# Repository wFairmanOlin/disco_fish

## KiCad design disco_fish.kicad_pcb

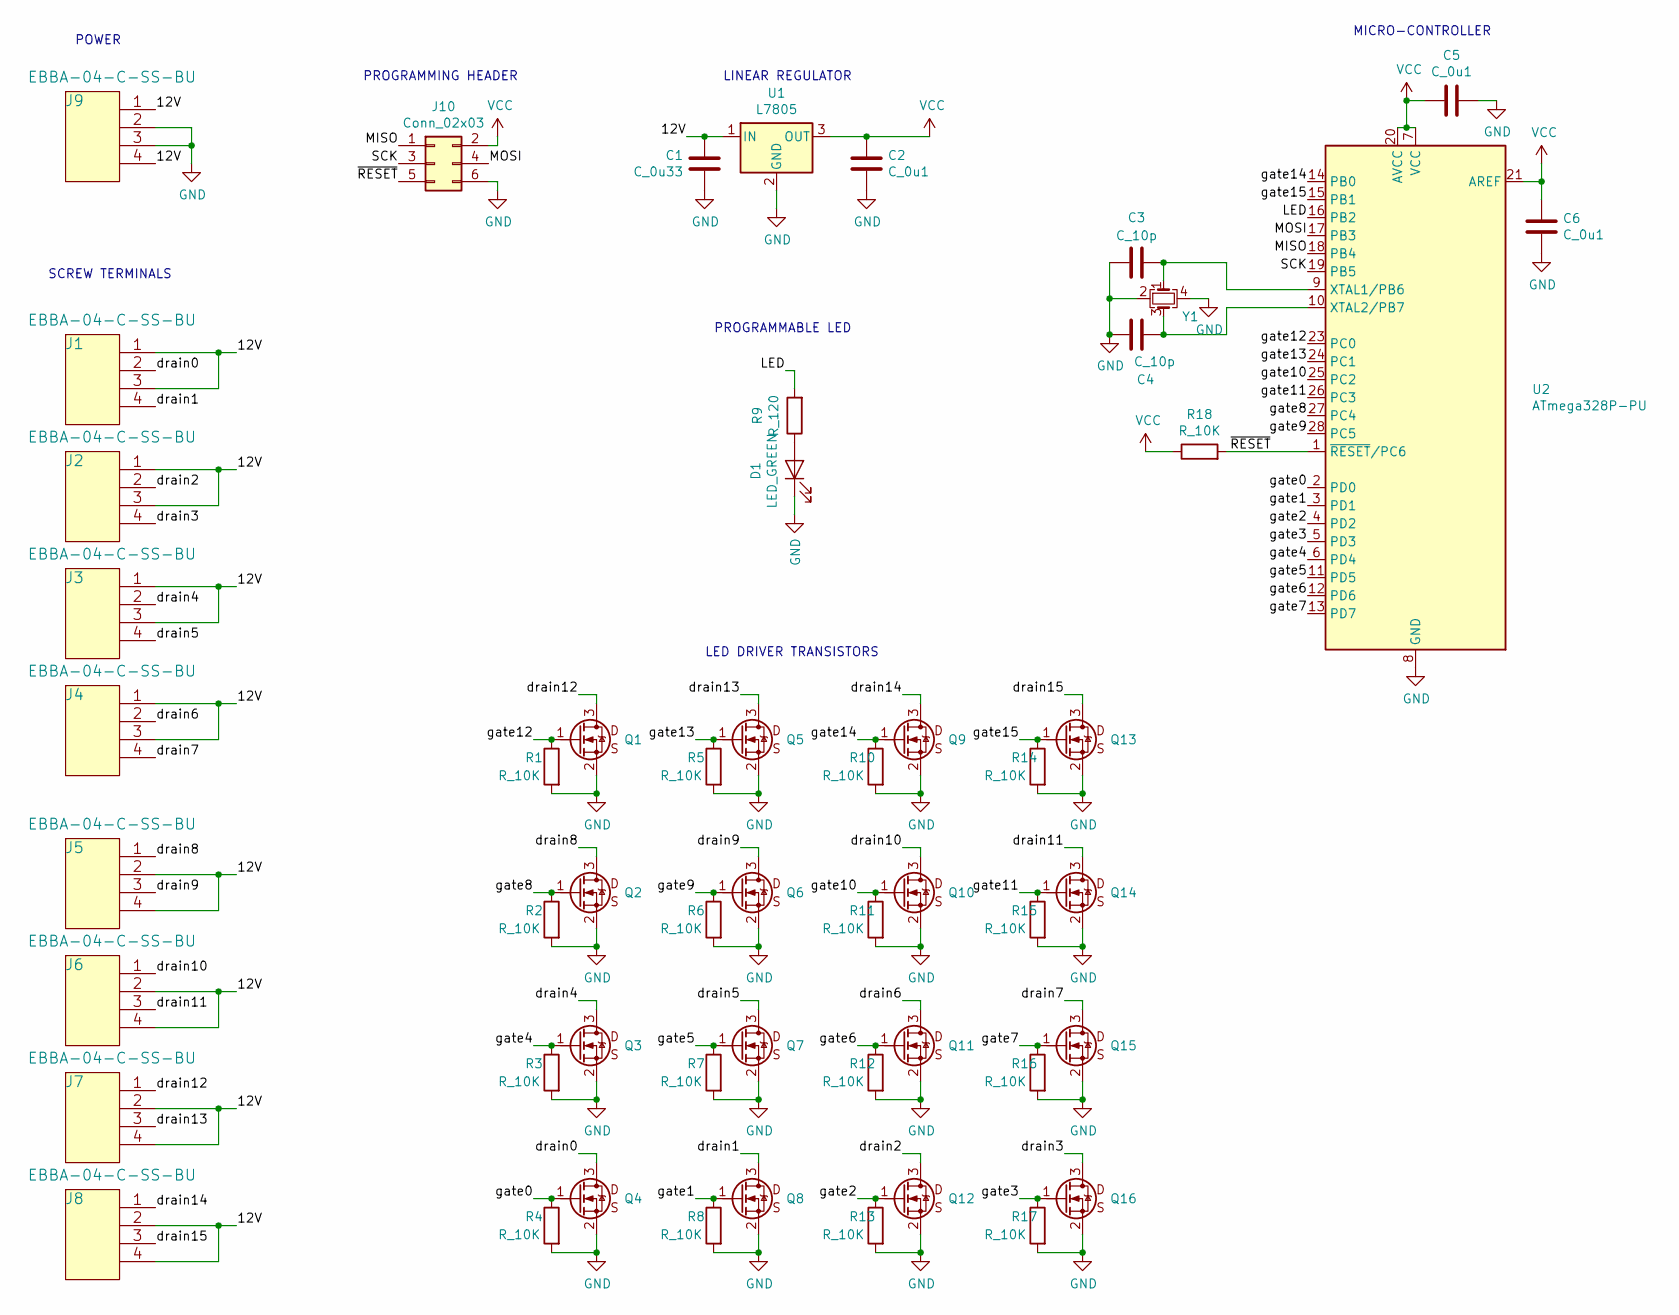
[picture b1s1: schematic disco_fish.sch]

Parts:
C1: C_0u33; C_0805; MPN CL21B334KBFNNNE
C2, C5, C6: C_0u1; C_0805
C3, C4: C_10p; C_0805; MPN 885012007010
D1: LED_GREEN; LED_0603_HandSoldering
J1, J2, J3, J4, J5, J6, J7, J8, J9: EBBA-04-C-SS-BU; MPN EBBA-04-C-SS-BU
J10: Conn_02x03; TSW-103-07-F-D; MPN TSW-103-07-F-D
Q1, Q2, Q3, Q4, Q5, Q6, Q7, Q8, Q9, Q10, Q11, Q12, Q13, Q14, Q15, Q16: NVS4409NT1G; SOT-323_SC-70; MPN NVS4409NT1G
R1, R2, R3, R4, R5, R6, R7, R8, R10, R11, R12, R13, R14, R15, R16, R17, R18: R_10K; R_0805; MPN RC0805FR-0710KL
R9: R_120; R_0805
U1: L7805; TO-252-2; MPN L7805CDT-TR
U2: ATmega328P-PU; DIP-28_W7.62mm; MPN ATMEGA328-PU
Y1: ECS-160-8-37-CWY-TR; 7M-16.000MAAJ-T; MPN ECS-160-8-37-CWY-TR

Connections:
/12V: C1.2, J1.1, J1.3, J2.1, J2.3, J3.1, J3.3, J4.1, J4.3, J5.2, J5.4, J6.2, J6.4, J7.2, J7.4, J8.2, J8.4, J9.1, J9.4, U1.1 (IN)
/LED: R9.2, U2.16 (PB2)
/MISO: J10.1, U2.18 (PB4)
/MOSI: J10.4, U2.17 (PB3)
/SCK: J10.3, U2.19 (PB5)
/drain0: J1.2, Q4.3
/drain1: J1.4, Q8.3
/drain2: J2.2, Q12.3
/drain3: J2.4, Q16.3
/drain4: J3.2, Q3.3
/drain5: J3.4, Q7.3
/drain6: J4.2, Q11.3
/drain7: J4.4, Q15.3
/drain8: J5.1, Q2.3
/drain9: J5.3, Q6.3
/drain10: J6.1, Q10.3
/drain11: J6.3, Q14.3
/drain12: J7.1, Q1.3
/drain13: J7.3, Q5.3
/drain14: J8.1, Q9.3
/drain15: J8.3, Q13.3
/gate0: Q4.1, R4.1, U2.2 (PD0)
/gate1: Q8.1, R8.1, U2.3 (PD1)
/gate2: Q12.1, R13.1, U2.4 (PD2)
/gate3: Q16.1, R17.1, U2.5 (PD3)
/gate4: Q3.1, R3.1, U2.6 (PD4)
/gate5: Q7.1, R7.1, U2.11 (PD5)
/gate6: Q11.1, R12.1, U2.12 (PD6)
/gate7: Q15.1, R16.1, U2.13 (PD7)
/gate8: Q2.1, R2.1, U2.27 (PC4)
/gate9: Q6.1, R6.1, U2.28 (PC5)
/gate10: Q10.1, R11.1, U2.25 (PC2)
/gate11: Q14.1, R15.1, U2.26 (PC3)
/gate12: Q1.1, R1.1, U2.23 (PC0)
/gate13: Q5.1, R5.1, U2.24 (PC1)
/gate14: Q9.1, R10.1, U2.14 (PB0)
/gate15: Q13.1, R14.1, U2.15 (PB1)
/~RESET: J10.5, R18.2, U2.1 (~RESET~/PC6)
GND: C1.1, C2.2, C3.2, C4.2, C5.1, C6.1, D1.1 (K), J9.2, J9.3, J10.6, Q1.2, Q2.2, Q3.2, Q4.2, Q5.2, Q6.2, Q7.2, Q8.2, Q9.2, Q10.2, Q11.2, Q12.2, Q13.2, Q14.2, Q15.2, Q16.2, R1.2, R2.2, R3.2, R4.2, R5.2, R6.2, R7.2, R8.2, R10.2, R11.2, R12.2, R13.2, R14.2, R15.2, R16.2, R17.2, U1.2 (GND), U2.8 (GND), U2.22 (GND), Y1.2, Y1.4
unnamed: C3.1, U2.9 (XTAL1/PB6), Y1.1
unnamed: C4.1, U2.10 (XTAL2/PB7), Y1.3
unnamed: D1.2 (A), R9.1
VCC: C2.1, C5.2, C6.2, J10.2, R18.1, U1.3 (OUT), U2.7 (VCC), U2.20 (AVCC), U2.21 (AREF)

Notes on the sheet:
PROGRAMMING HEADER
LINEAR REGULATOR
LED DRIVER TRANSISTORS
PROGRAMMABLE LED
MICRO-CONTROLLER
POWER
SCREW TERMINALS

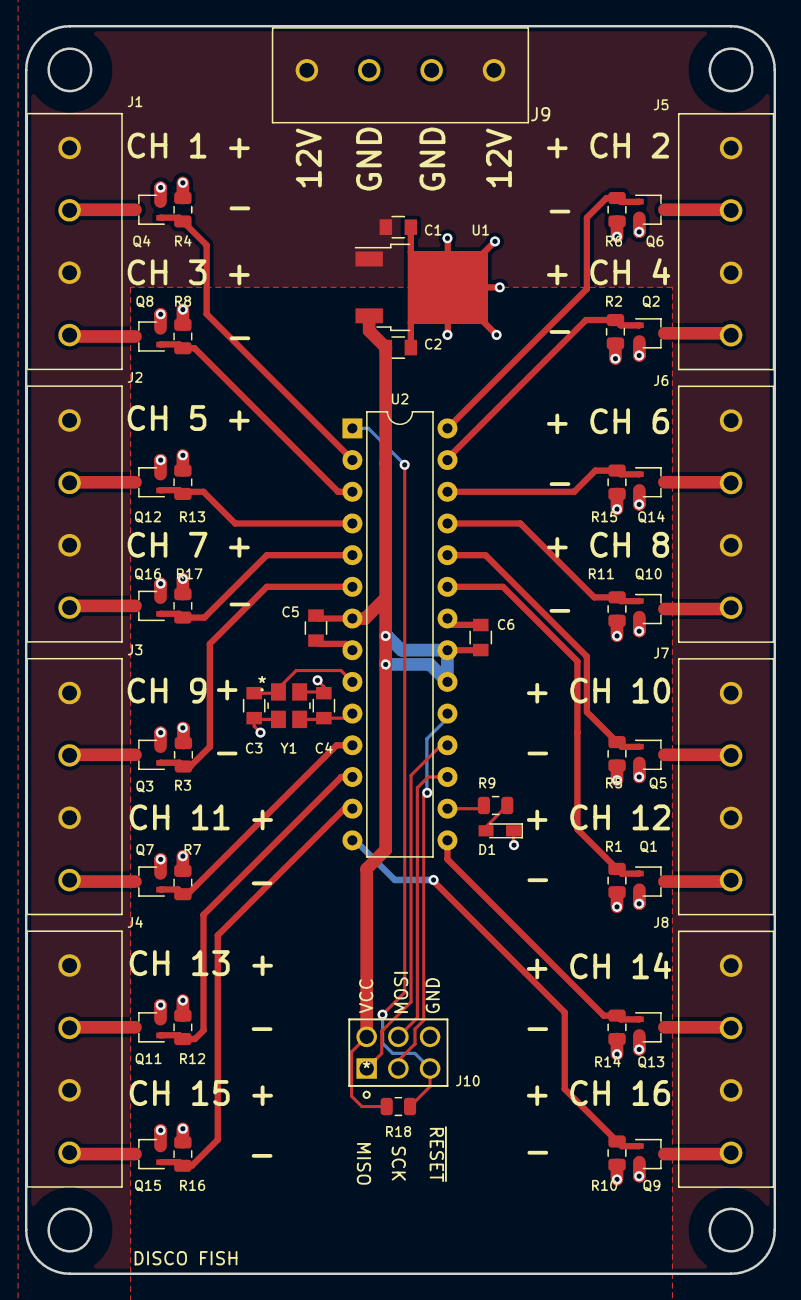
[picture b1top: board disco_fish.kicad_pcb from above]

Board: 2 copper layers, 60.0 x 100.0 mm, 54 parts (0 on the bottom side), 43 nets.

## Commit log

2021-06-27 finished pcb
2021-06-30 finalized design
